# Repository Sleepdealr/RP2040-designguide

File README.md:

# Hardware design for the RP2040

This guide requires you to have prerequisite knowledge about PCB design and a little about the RP2040. This is not a guide for absolute beginners and should not be treated as one.

I have multiple tested and working boards using the RP2040, including an open source one you can find [here](https://github.com/Sleepdealr/RPAD)!

Bit of a disclaimer: I have mostly switched from RP2040 over to STM32F072 due to a few reasons. Mostly component cost and the amount of parts necessary, as well as overall stability. I have a tested and OSH f072 PCBs available on github. Namely [here](https://github.com/Sleepdealr/Majestouch-2-TKL-Replacement-Controller), [here](https://github.com/Sleepdealr/OSFRL), and [here](https://github.com/Sleepdealr/Kingsaver-Replacement-PCB). Designing with f072 is generally easier as well, so I would suggest it even for beginners.

## Contents

- [Hardware design for the RP2040](#hardware-design-for-the-rp2040)
  - [Contents](#contents)
  - [KiCad Version](#kicad-version)
  - [Libraries](#libraries)
  - [Extra Resources](#extra-resources)
  - [Schematic](#schematic)
    - [Component Choices](#component-choices)
      - [Voltage Regulator](#voltage-regulator)
      - [Crystal](#crystal)
      - [Flash](#flash)
      - [Pushbuttons](#pushbuttons)
  - [PCB](#pcb)
    - [Placement / Routing](#placement--routing)
    - [BOM](#bom)
  - [Firmware](#firmware)
    - [Flashing QMK on Linux from CLI](#flashing-qmk-on-linux-from-cli)
  - [Extra info](#extra-info)
    - [EEPROM](#eeprom)
  - [Too Complicated?](#too-complicated)

## KiCad Version

To open these files, you will need a recent stable version of KiCad (6.0 or later).

Stop using KiCad 5.X, it's out of date

## Libraries

You can either import them into your own library or keep them separate.

- Symbol:
  - Created by me to be easier to use
  - `/PCB/Libraries/Sleep-lib`
- Footprint:
  - Taken from Raspberry
  - `/PCB/Libraries/Footprints/RP2040-QFN-56.kicad_mod`
  - 3D Model is included

Images of the 3DView, EEschema, and PCBNew in the `/img` folder.

## Extra Resources

All the other information I found about the chip is in in the `/Pico-Resources` Folder

## Schematic

[PDF of schematic](PCB/RP2040-Guide.pdf)

THIS IMAGE WILL BE OUT OF DATE. LOOK AT THE PDF FOR THE LATEST VERSION.

If you want to know more about the components choices, read the section below or Raspberry's hardware design example.
The PDF is `/Pico-Resources/hardware-design-with-rp2040.pdf`.

I would also recommend reading my [Best practices for PCB Design](https://gist.github.com/Sleepdealr/ab05f5edb82eae9e0393f4d63da55adf) guide before making your own schematic or PCB

Breakout for SWD/GPIO is NOT required.

### Component Choices

Trust me on these pls

#### Voltage Regulator

Use the XC6206, it's a basic part on JLC. The 200mA it provides is plenty for the RP2040.

The AMS1117 has high quiescent current, needs large caps, and has a bad minimum load. Don't use it.

#### Crystal

C9002 is a great basic part for a 12MHz 3225 crystal

#### Flash

There are a ton of options for flash, but I tend to stick with C82317 as it's a basic part and has a good price. More than enough flash for any keyboard.

#### Pushbuttons

Although I didn't use a button on the included PCB files, you can easily add one yourself. A good cheap button that fits the Alps SKQG footprint is C318884.

####

## PCB

THIS IMAGE WILL BE OUT OF DATE. LOOK AT THE KiCad FILES FOR THE LATEST VERSION.

### Placement / Routing

- Fills inside of the MCU were taken from the design example. You can just copy paste them out. Make sure to set the correct zone priority and clearances. Zones are filled from high to low numbers.
- Keep the decoupling capacitors close to their respective pins.
- Keep the flash and crystal as close as possible to the MCU with minimal overlaps and vias
  - If anything, just copy paste from my files
- I would suggest including an actual switch for USB BOOT or RESET on to make it easier to flash, but that's up to you.

### BOM

- Everything on the PCB can be assembled by JLC, all the part numbers have been added to the components with the Kicad JLCPCB plugin
- I have tested and working JLC part numbers for all of the components, but check the stock levels and prices first before ordering. There may be a better alternative available
- There are a few different flash sizes and packages to choose from. All of them should work pretty much the same, since firmware size is not an issue. I usually just go with the cheapest option

## Firmware

Both QMK and Vial have support for RP2040 in their master branches. Make sure to check the features you want before designing

- QMK
  - QMK Main Branch: <https://github.com/qmk/qmk_firmware/>
  - RP2040 available features: <https://docs.qmk.fm/#/platformdev_rp2040?id=raspberry-pi-rp2040>
- Vial
  - Vial Main Branch: <https://github.com/vial-kb/vial-qmk/>
- KMK
  - <https://github.com/KMKfw/kmk_firmware>
- Keyberon
  - <https://github.com/TeXitoi/keyberon>

To flash, hold the USB-BOOT button down as you plug in the keyboard (like Bootmagic reset)

### Flashing QMK on Linux from CLI

You will need to install picotool with your distro's package manager of choice, or [build it manually](https://github.com/raspberrypi/picotool#building).

In order to be able to flash properly, you will need to configure a custom udev rule.

Open a terminal and execute this script.

```bash
sudo mkdir -p /etc/udev/rules.d/
echo '# /etc/udev/rules.d/99-pico.rules

# Make an RP2040 in BOOTSEL mode writable by all users, so you can `picotool`
# without `sudo`.
SUBSYSTEM=="usb", ATTRS{idVendor}=="2e8a", ATTRS{idProduct}=="0003", MODE="0666"

# Symlink an RP2040 running MicroPython from /dev/pico.
#
# Then you can `mpr connect $(realpath /dev/pico)`.
SUBSYSTEM=="tty", ATTRS{idVendor}=="2e8a", ATTRS{idProduct}=="0005", SYMLINK+="pico"", TAG+="uaccess", TAG+="udev-acl"' | sudo tee /etc/udev/rules.d/99-pico.rules
sudo udevadm control --reload-rules
sudo udevadm trigger
```

Command borrowed from xyz's VIAL docs

## Extra info

### EEPROM

While the Raspberry Pi Pico RP2040 does not come with an EEPROM onboard, we simulate one by using a single 4K chunk of flash at the end of flash space.

**Note that this is a simulated EEPROM and will only support the number of writes as the onboard flash chip, not the 100,000 or so of a real EEPROM.** Therefore, do not frequently update the EEPROM or you may prematurely wear out the flash.

Source: <https://arduino-pico.readthedocs.io/en/latest/eeprom.html>

This isn't really an issue, as the flash chip I used is rated for 100k cycles [link to datasheet](https://www.winbond.com/resource-files/w25q128jv_dtr%20revc%2003272018%20plus.pdf)

## Too Complicated?

If all of this seems too daunting, my commissions are open! You can contact me on discord at Sleepdealer#0001 or through email at sleepdealer01@protonmail.com

Portfolio: <https://sleepdealer.xyz/article/portfolio>

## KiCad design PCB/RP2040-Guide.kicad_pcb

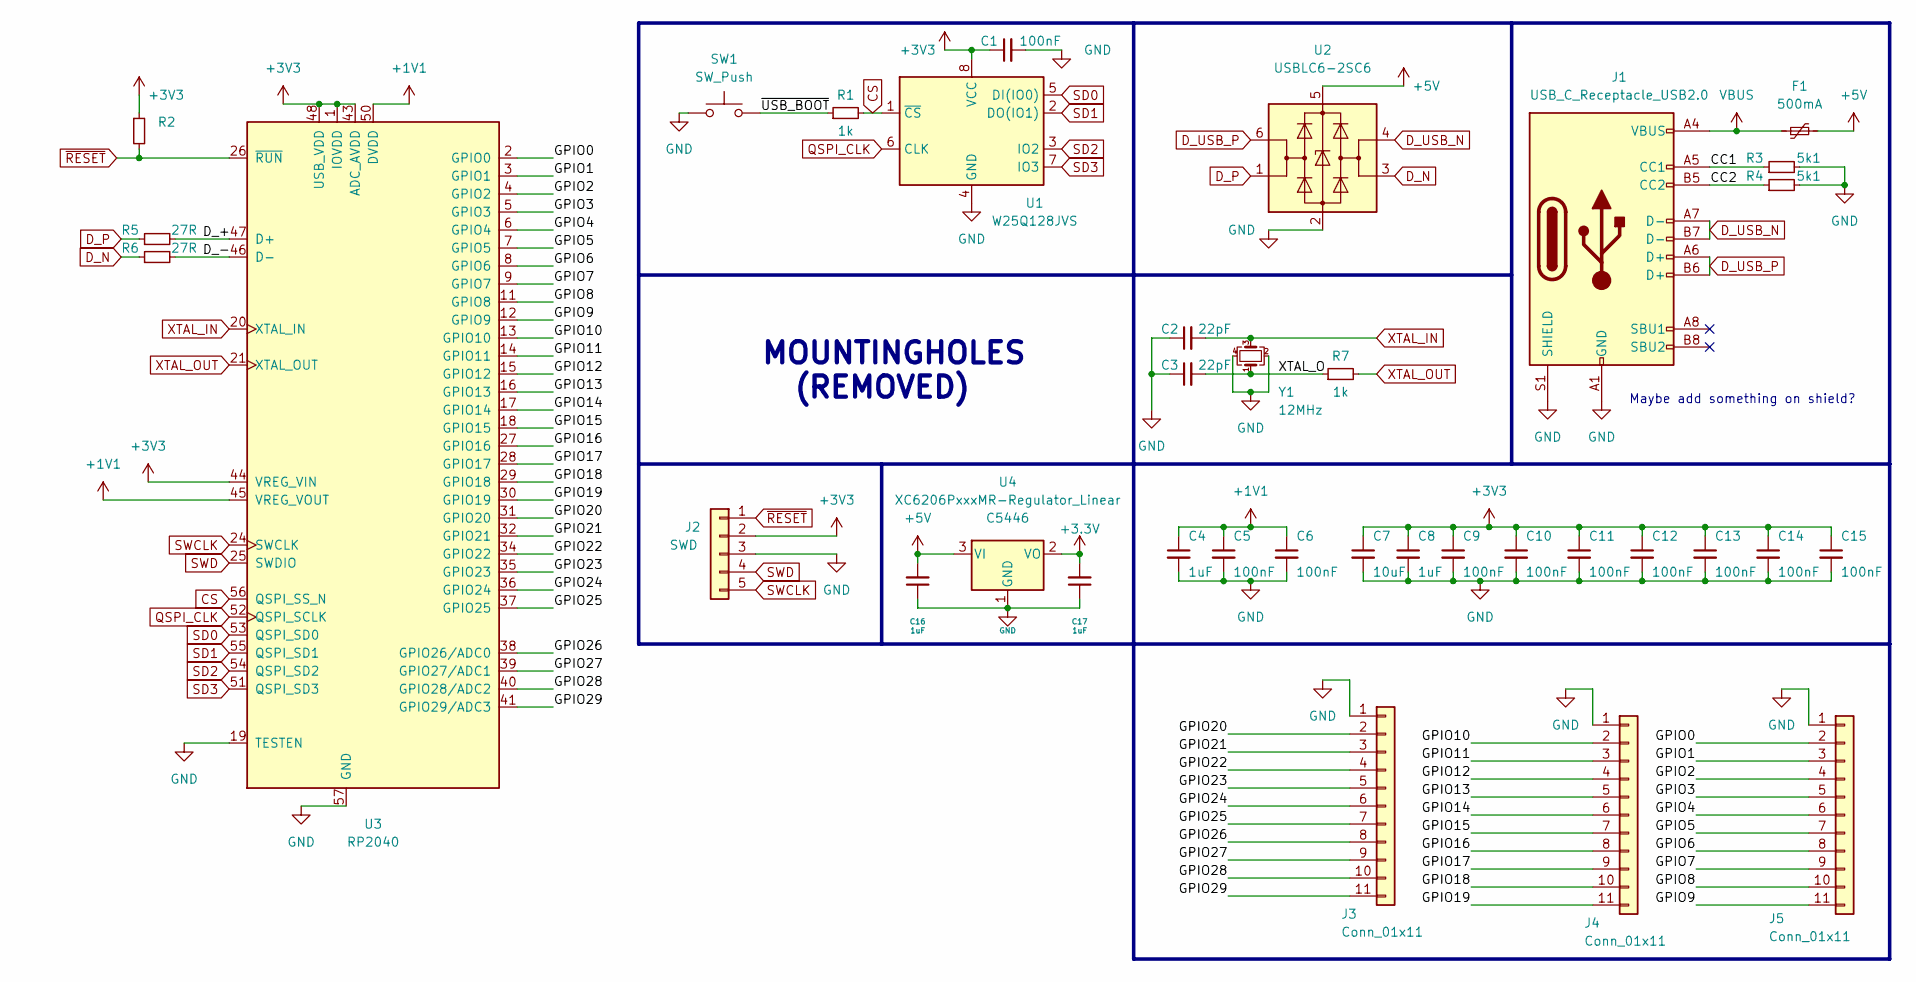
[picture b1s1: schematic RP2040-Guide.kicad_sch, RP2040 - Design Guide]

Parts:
C1, C5, C6, C9, C10, C11, C12, C13, C14, C15: 100nF; C_0402_1005Metric; LCSC C1525
C2, C3: 22pF; C_0402_1005Metric; LCSC C1555
C4, C8, C16, C17: 1uF; C_0402_1005Metric; LCSC C52923
C7: 10uF; C_0402_1005Metric; LCSC C15525
F1: 500mA; Fuse_1206_3216Metric; LCSC C70076
J1: USB_C_Receptacle_USB2.0; USB_C_Receptacle_HRO_TYPE-C-31-M-12; LCSC C165948
J2: SWD; PinSocket_1x05_P2.54mm_Vertical
J3, J4, J5: Conn_01x11; PinSocket_1x11_P2.54mm_Vertical
R1, R7: 1k; R_0402_1005Metric; LCSC C11702
R2: LCSC C11702
R3, R4: 5k1; R_0402_1005Metric; LCSC C25905
R5, R6: 27R; R_0603_1608Metric; LCSC C25190
SW1: SW_Push; PinSocket_1x02_P2.54mm_Vertical
U1: W25Q128JVS; SOIC-8_5.23x5.23mm_P1.27mm; LCSC C131025
U2: USBLC6-2SC6; SOT-23-6; LCSC C2827654
U3: RP2040; RP2040-QFN-56; LCSC C2040
U4: XC6206PxxxMR-Regulator_Linear; SOT-23; LCSC C5446
Y1: 12MHz; Crystal_SMD_3225-4Pin_3.2x2.5mm; LCSC C9002

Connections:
+1V1: C4.1, C5.1, C6.1, U3.23 (DVDD), U3.45 (VREG_VOUT), U3.50 (DVDD)
+5V: C16.2, F1.2, U2.5 (VBUS), U4.3 (VI)
/CC1: J1.A5 (CC1), R3.1
/CC2: J1.B5 (CC2), R4.1
/D_+: R5.2, U3.47 (D+)
/D_-: R6.2, U3.46 (D-)
/GPIO0: J5.2, U3.2 (GPIO0)
/GPIO1: J5.3, U3.3 (GPIO1)
/GPIO2: J5.4, U3.4 (GPIO2)
/GPIO3: J5.5, U3.5 (GPIO3)
/GPIO4: J5.6, U3.6 (GPIO4)
/GPIO5: J5.7, U3.7 (GPIO5)
/GPIO6: J5.8, U3.8 (GPIO6)
/GPIO7: J5.9, U3.9 (GPIO7)
/GPIO8: J5.10, U3.11 (GPIO8)
/GPIO9: J5.11, U3.12 (GPIO9)
/GPIO10: J4.2, U3.13 (GPIO10)
/GPIO11: J4.3, U3.14 (GPIO11)
/GPIO12: J4.4, U3.15 (GPIO12)
/GPIO13: J4.5, U3.16 (GPIO13)
/GPIO14: J4.6, U3.17 (GPIO14)
/GPIO15: J4.7, U3.18 (GPIO15)
/GPIO16: J4.8, U3.27 (GPIO16)
/GPIO17: J4.9, U3.28 (GPIO17)
/GPIO18: J4.10, U3.29 (GPIO18)
/GPIO19: J4.11, U3.30 (GPIO19)
/GPIO20: J3.2, U3.31 (GPIO20)
/GPIO21: J3.3, U3.32 (GPIO21)
/GPIO22: J3.4, U3.34 (GPIO22)
/GPIO23: J3.5, U3.35 (GPIO23)
/GPIO24: J3.6, U3.36 (GPIO24)
/GPIO25: J3.7, U3.37 (GPIO25)
/GPIO26: J3.8, U3.38 (GPIO26/ADC0)
/GPIO27: J3.9, U3.39 (GPIO27/ADC1)
/GPIO28: J3.10, U3.40 (GPIO28/ADC2)
/GPIO29: J3.11, U3.41 (GPIO29/ADC3)
/XTAL_O: C3.2, R7.1, Y1.1
/~USB_BOOT: R1.1, SW1.2
CS: R1.2, U1.1 (~CS), U3.56 (QSPI_SS_N)
D_N: R6.1, U2.3 (I/O2)
D_P: R5.1, U2.1 (I/O1)
D_USB_N: J1.A7 (D-), J1.B7 (D-), U2.4 (I/O2)
D_USB_P: J1.A6 (D+), J1.B6 (D+), U2.6 (I/O1)
GND: C1.2, C2.1, C3.1, C4.2, C5.2, C6.2, C7.2, C8.2, C9.2, C10.2, C11.2, C12.2, C13.2, C14.2, C15.2, C16.1, C17.1, J1.A1 (GND), J1.A12 (GND), J1.B1 (GND), J1.B12 (GND), J1.S1 (SHIELD), J2.3, J3.1, J4.1, J5.1, R3.2, R4.2, SW1.1, U1.4 (GND), U2.2 (GND), U3.19 (TESTEN), U3.57 (GND), U4.1 (GND), Y1.2, Y1.4
QSPI_CLK: U1.6 (CLK), U3.52 (QSPI_SCLK)
SD0: U1.5 (DI(IO0)), U3.53 (QSPI_SD0)
SD1: U1.2 (DO(IO1)), U3.55 (QSPI_SD1)
SD2: U1.3 (IO2), U3.54 (QSPI_SD2)
SD3: U1.7 (IO3), U3.51 (QSPI_SD3)
SWCLK: J2.5, U3.24 (SWCLK)
SWD: J2.4, U3.25 (SWDIO)
VBUS: F1.1, J1.A4 (VBUS), J1.A9 (VBUS), J1.B4 (VBUS), J1.B9 (VBUS)
XTAL_IN: C2.2, U3.20 (XTAL_IN), Y1.3
XTAL_OUT: R7.2, U3.21 (XTAL_OUT)
~RESET: J2.1, R2.2, U3.26 (~RUN)

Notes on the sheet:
MOUNTINGHOLES (REMOVED)
Maybe add something on shield?

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
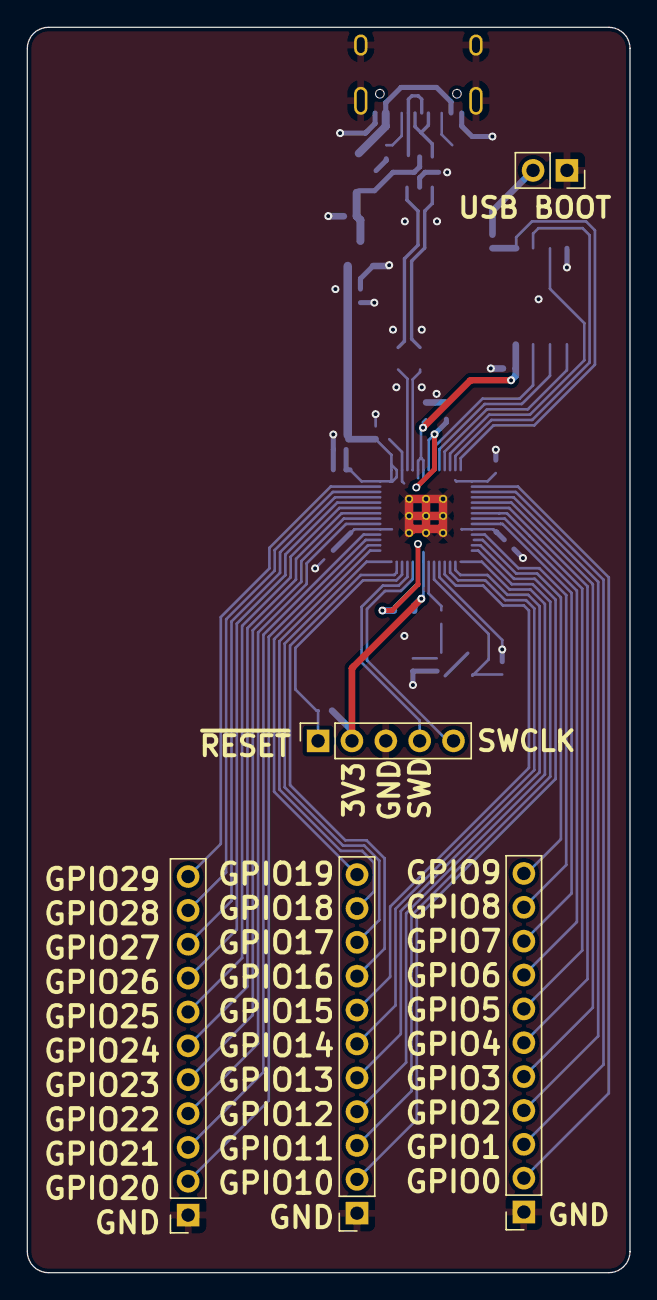
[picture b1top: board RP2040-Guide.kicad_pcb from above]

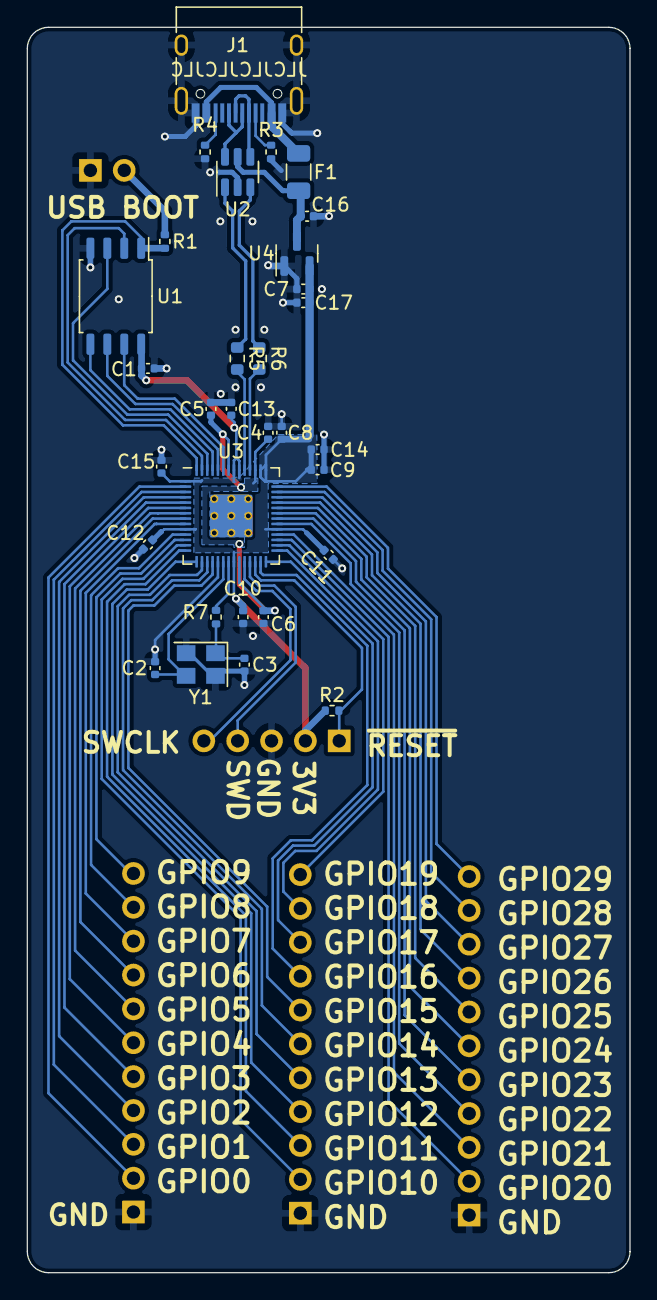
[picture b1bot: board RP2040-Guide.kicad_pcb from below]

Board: 2 copper layers, 45.2 x 93.4 mm, 36 parts (31 on the bottom side), 56 nets.

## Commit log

2021-12-08 Remove old firmware and duplicated libs
2021-12-08 Add RP2040 STEP file
2021-12-08 Edit formatting on readme/pcb/schematic
2021-12-08 I hate documentation
2021-12-08 Talk about images
2021-12-08 Updated images to take up less space
2021-12-08 Add images to README
2021-12-18 Adding some more to the guide
2021-12-18 Fixing readme (again)
2021-12-18 Extra eeprom info
2021-12-26 Update guide (Thanks xyz!)
2022-03-13 Update BOM and borked vias (Thanks to SpeedyPotato!)
2022-05-27 Update guide a bit
2022-05-27 fix premature push
2022-05-27 Edit a bunch of stuff
2022-05-27 fixed typo
2022-06-13 Fix Grammar
2022-06-13 (for real this time)
2022-08-31 i'm not procrastinating
2022-08-31 forgot a word
2023-02-13 Small edits
